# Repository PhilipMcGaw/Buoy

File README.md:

# Buoy

https://github.com/sk-t3ch/smart-buoy

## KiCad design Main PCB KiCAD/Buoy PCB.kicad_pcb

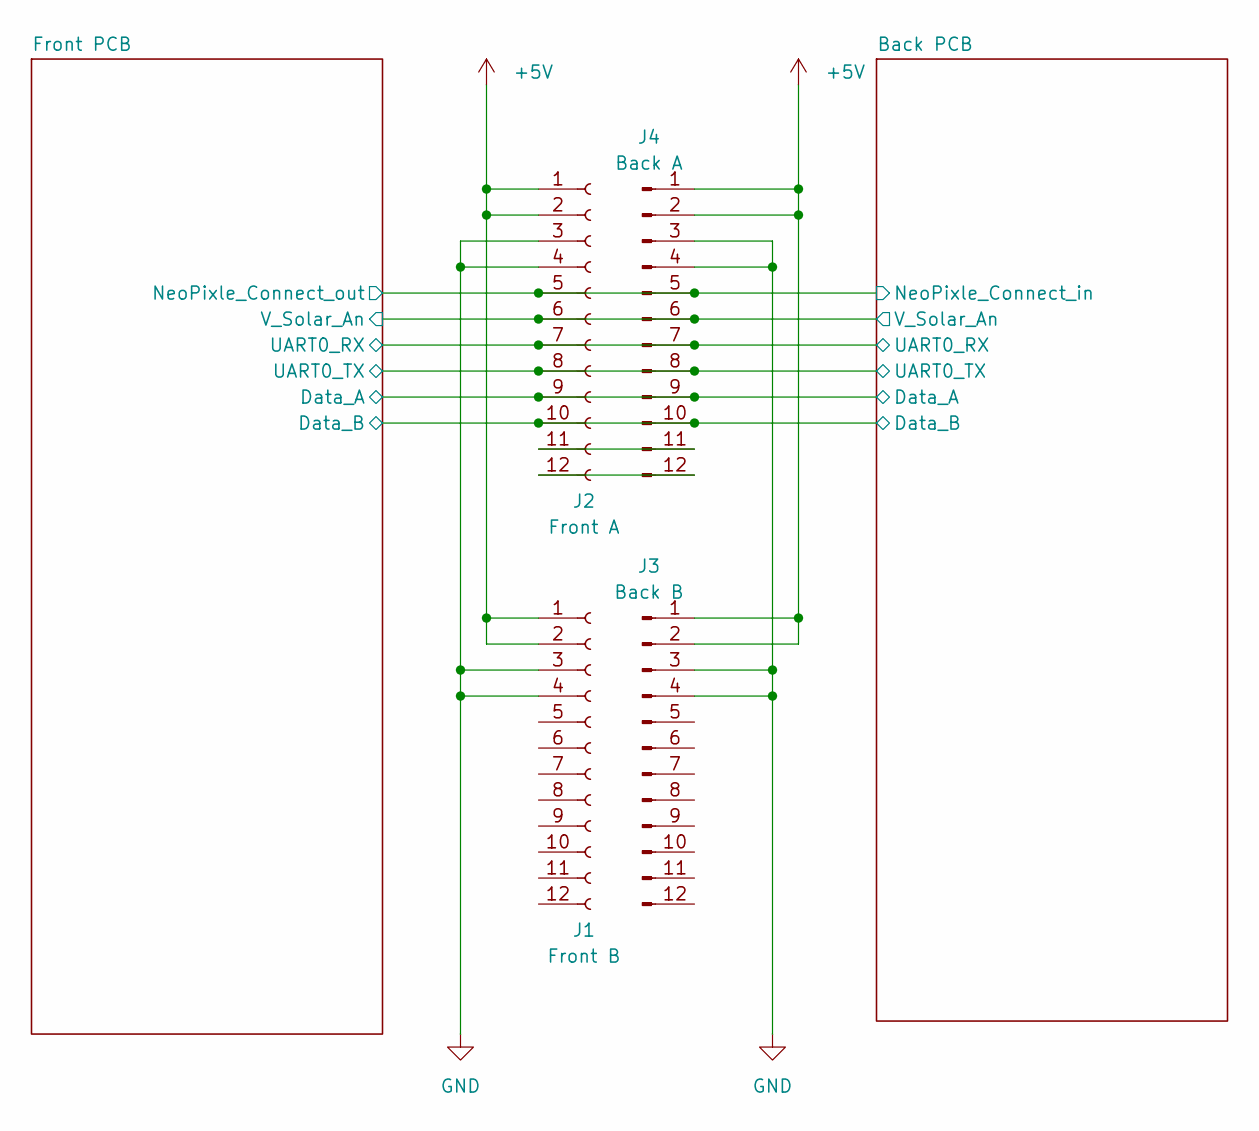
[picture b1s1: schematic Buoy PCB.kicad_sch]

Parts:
J1: Front B; PinSocket_1x12_P2.54mm_Vertical
J2: Front A; PinSocket_1x12_P2.54mm_Vertical
J3: Back B; PinHeader_1x12_P2.54mm_Vertical
J4: Back A; PinHeader_1x12_P2.54mm_Vertical

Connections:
+5V: J1.1, J1.2, J2.1, J2.2, J3.1, J3.2, J4.1, J4.2; also elsewhere on the board
/Back PCB/Data_A: J2.9, J4.9; also elsewhere on the board
/Back PCB/Data_B: J2.10, J4.10; also elsewhere on the board
/Back PCB/NeoPixle_Connect_in: J2.5, J4.5; also elsewhere on the board
/Back PCB/UART0_RX: J2.7, J4.7; also elsewhere on the board
/Back PCB/UART0_TX: J2.8, J4.8; also elsewhere on the board
/Back PCB/V_Solar_An: J2.6, J4.6; also elsewhere on the board
GND: J1.3, J1.4, J2.3, J2.4, J3.3, J3.4, J4.3, J4.4; also elsewhere on the board
unnamed: J2.11, J4.11
unnamed: J2.12, J4.12

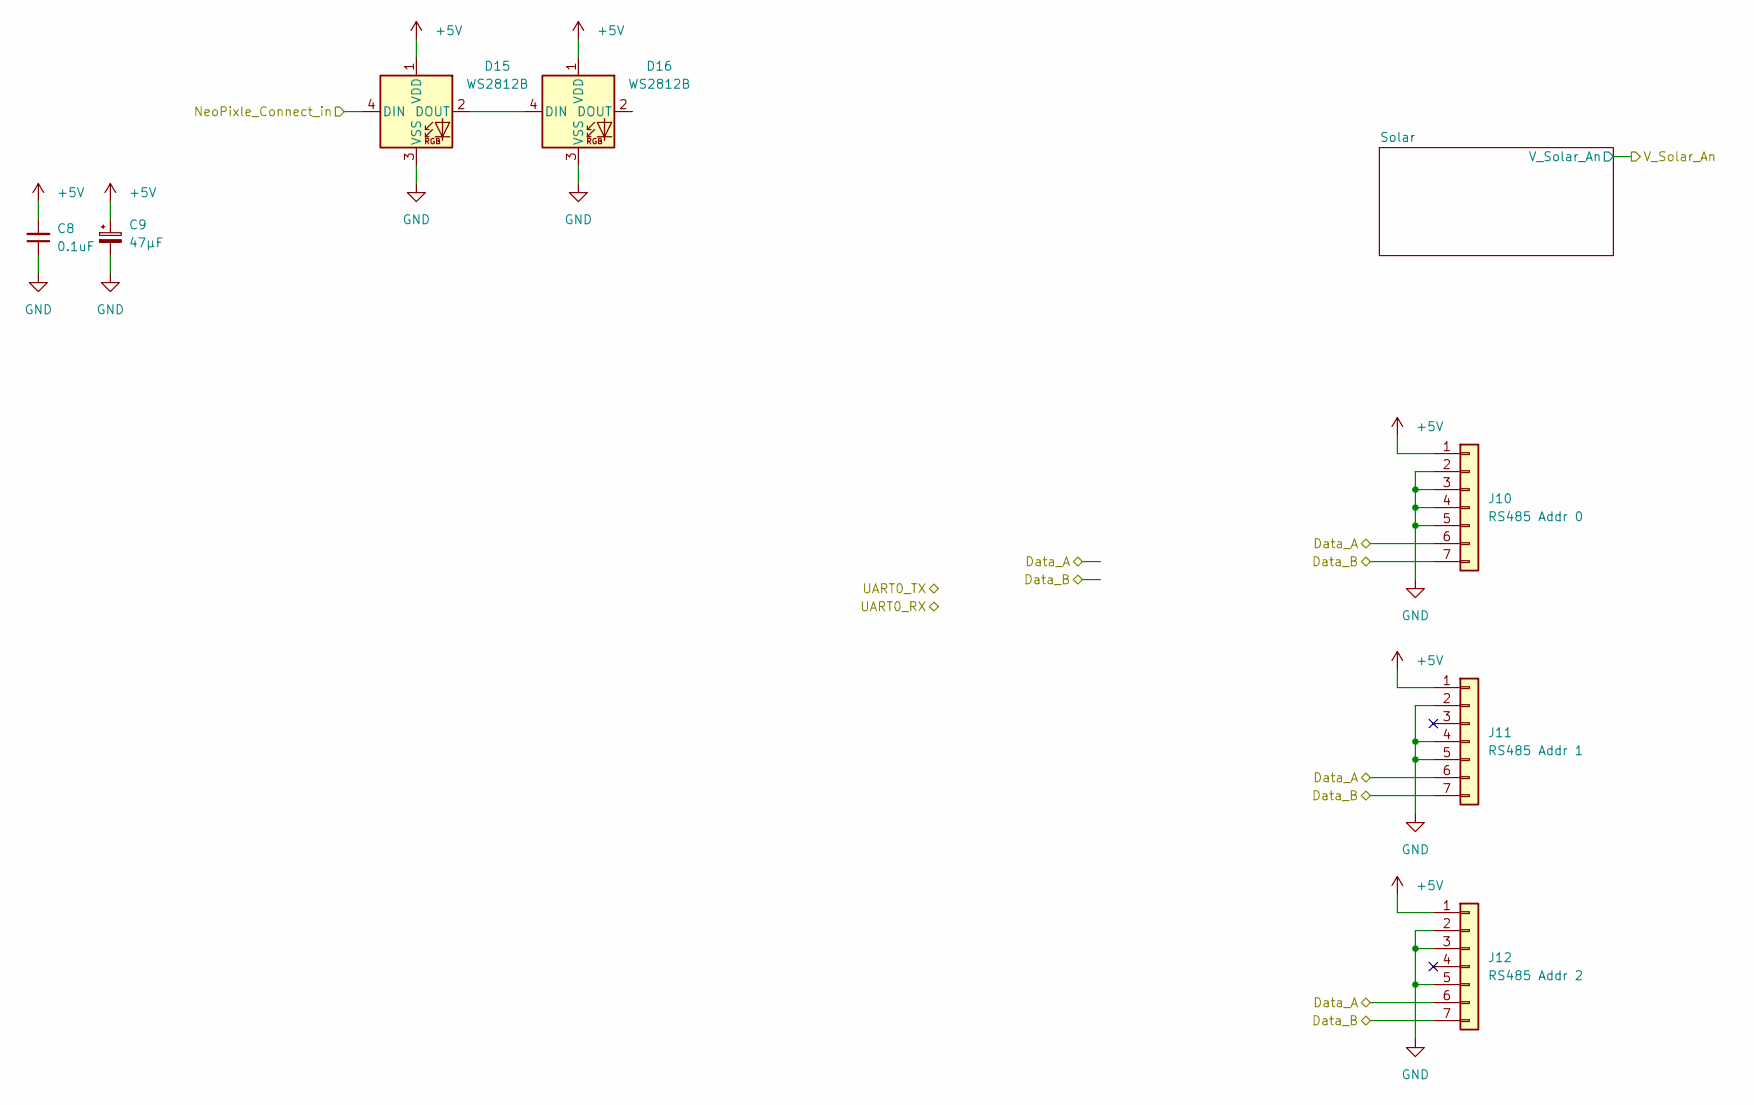
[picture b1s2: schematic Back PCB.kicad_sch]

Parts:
C8: 0.1uF; C_0805_2012Metric_Pad1.18x1.45mm_HandSolder
C9: 47μF; CP_Elec_5x5.9
D15, D16: WS2812B; LED_WS2812B_PLCC4_5.0x5.0mm_P3.2mm
J10: RS485 Addr 0; JST_EH_S7B-EH_1x07_P2.50mm_Horizontal
J11: RS485 Addr 1; JST_EH_S7B-EH_1x07_P2.50mm_Horizontal
J12: RS485 Addr 2; JST_EH_S7B-EH_1x07_P2.50mm_Horizontal

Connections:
+5V: C8.2, C9.1, D15.1 (VDD), D16.1 (VDD), J10.1, J11.1, J12.1; also elsewhere on the board
/Back PCB/Data_A: J10.6, J11.6, J12.6; also elsewhere on the board
/Back PCB/Data_B: J10.7, J11.7, J12.7; also elsewhere on the board
/Back PCB/NeoPixle_Connect_in: D15.4 (DIN); also elsewhere on the board
GND: C8.1, C9.2, D15.3 (VSS), D16.3 (VSS), J10.2, J10.3, J10.4, J10.5, J11.2, J11.4, J11.5, J12.2, J12.3, J12.5; also elsewhere on the board
unnamed: D15.2 (DOUT), D16.4 (DIN)

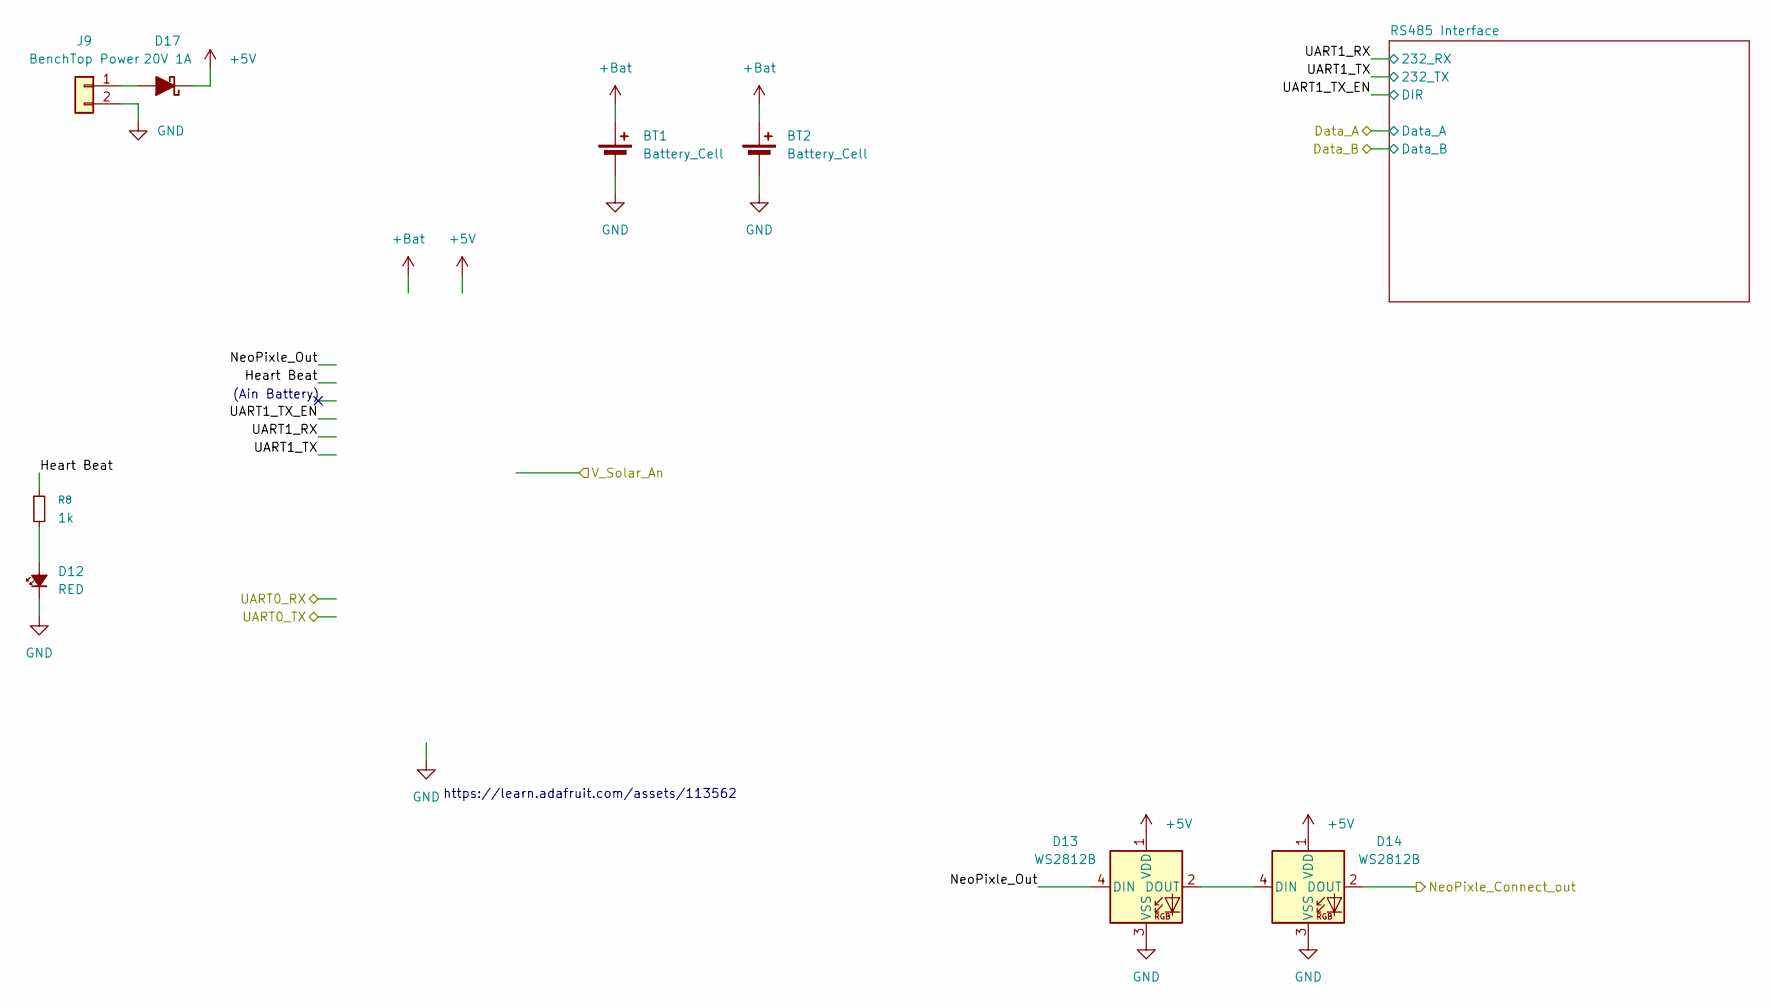
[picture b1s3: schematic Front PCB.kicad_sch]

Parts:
BT1, BT2: Battery_Cell; BatteryHolder_Keystone_1042_1x18650
D12: RED; LED_0805_2012Metric_Pad1.15x1.40mm_HandSolder
D13, D14: WS2812B; LED_WS2812B_PLCC4_5.0x5.0mm_P3.2mm
D17: 20V 1A; D_0805_2012Metric_Pad1.15x1.40mm_HandSolder; Mouser 581-SD0805S020S1R0
J9: BenchTop Power; JST_EH_S2B-EH_1x02_P2.50mm_Horizontal
R8: 1k; R_0805_2012Metric_Pad1.20x1.40mm_HandSolder

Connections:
+5V: D13.1 (VDD), D14.1 (VDD), D17.1 (K); also elsewhere on the board
+Bat: BT1.1 (+), BT2.1 (+); also elsewhere on the board
/Back PCB/NeoPixle_Connect_in: D14.2 (DOUT); also elsewhere on the board
/Front PCB/Heart Beat: R8.1; also elsewhere on the board
/Front PCB/NeoPixle_Out: D13.4 (DIN); also elsewhere on the board
GND: BT1.2 (-), BT2.2 (-), D12.1 (K), D13.3 (VSS), D14.3 (VSS), J9.2; also elsewhere on the board
unnamed: D12.2 (A), R8.2
unnamed: D13.2 (DOUT), D14.4 (DIN)
unnamed: D17.2 (A), J9.1

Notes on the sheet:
(Ain Battery)
https://learn.adafruit.com/assets/113562

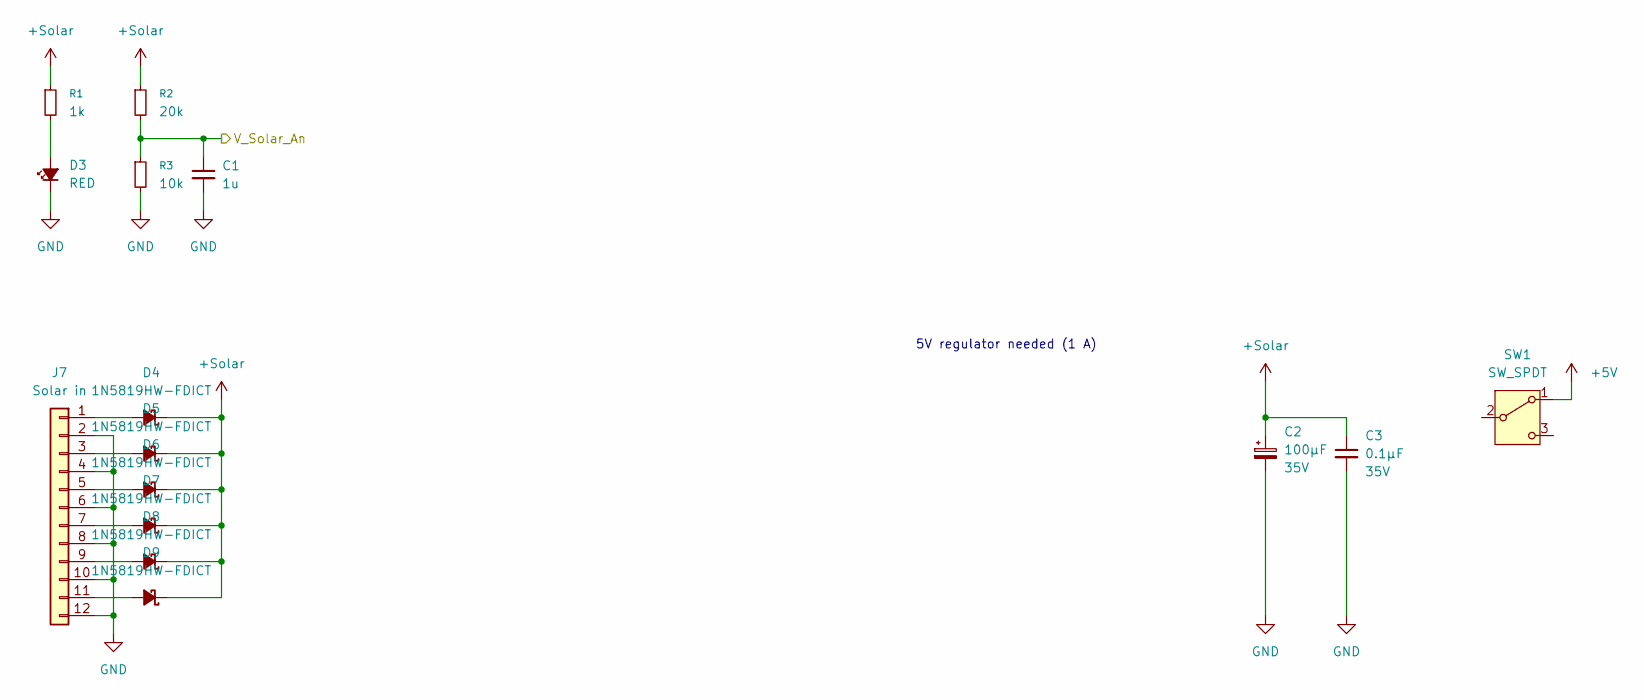
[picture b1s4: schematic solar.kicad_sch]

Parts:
C1: 1u; C_0805_2012Metric_Pad1.18x1.45mm_HandSolder
C2: 100μF; CP_Elec_5x5.9; Voltage 35V; Farnell 2690258
C3: 0.1μF; C_0805_2012Metric_Pad1.18x1.45mm_HandSolder; Voltage 35V; Farnell 2773206
D3: RED; LED_0805_2012Metric_Pad1.15x1.40mm_HandSolder
D4, D5, D6, D7, D8, D9: 1N5819HW-FDICT; D_SOD-123
J7: Solar in; JST_EH_S12B-EH_1x12_P2.50mm_Horizontal
R1: 1k; R_0805_2012Metric_Pad1.20x1.40mm_HandSolder
R2: 20k; R_0805_2012Metric_Pad1.20x1.40mm_HandSolder
R3: 10k; R_0805_2012Metric_Pad1.20x1.40mm_HandSolder
SW1: SW_SPDT; SW_Slide_SPDT_Angled_CK_OS102011MA1Q

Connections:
+5V: SW1.1 (A_1); also elsewhere on the board
+Solar: C2.1, C3.1, D4.1 (K), D5.1 (K), D6.1 (K), D7.1 (K), D8.1 (K), D9.1 (K), R1.1, R2.1
/Back PCB/V_Solar_An: C1.1, R2.2, R3.1; also elsewhere on the board
GND: C1.2, C2.2, C3.2, D3.1 (K), J7.2, J7.4, J7.6, J7.8, J7.10, J7.12, R3.2; also elsewhere on the board
unnamed: D3.2 (A), R1.2
unnamed: D4.2 (A), J7.1
unnamed: D5.2 (A), J7.3
unnamed: D6.2 (A), J7.5
unnamed: D7.2 (A), J7.7
unnamed: D8.2 (A), J7.9
unnamed: D9.2 (A), J7.11

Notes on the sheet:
5V regulator needed (1 A)

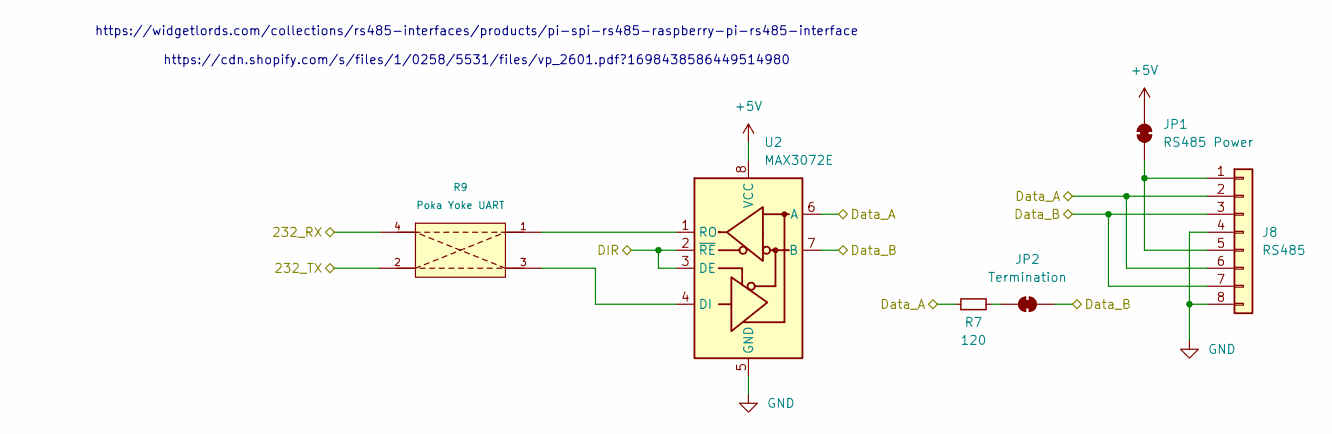
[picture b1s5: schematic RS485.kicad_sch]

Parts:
J8: RS485; JST_EH_S8B-EH_1x08_P2.50mm_Horizontal
JP1: RS485 Power; SolderJumper-2_P1.3mm_Bridged_RoundedPad1.0x1.5mm
JP2: Termination; SolderJumper-2_P1.3mm_Bridged_RoundedPad1.0x1.5mm
R7: 120; R_0805_2012Metric_Pad1.20x1.40mm_HandSolder
R9: Poka Yoke UART; Poka yoke UART Solder
U2: MAX3072E; SOIC-8_3.9x4.9mm_P1.27mm

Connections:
+5V: JP1.2 (B), U2.8 (VCC); also elsewhere on the board
/Back PCB/Data_A: J8.2, J8.6, R7.1, U2.6 (A); also elsewhere on the board
/Back PCB/Data_B: J8.3, J8.7, JP2.1 (A), U2.7 (B); also elsewhere on the board
/Front PCB/UART1_RX: R9.4; also elsewhere on the board
/Front PCB/UART1_TX: R9.2; also elsewhere on the board
/Front PCB/UART1_TX_EN: U2.2 (~RE), U2.3 (DE); also elsewhere on the board
GND: J8.4, J8.8, U2.5 (GND); also elsewhere on the board
unnamed: J8.1, J8.5, JP1.1 (A)
unnamed: JP2.2 (B), R7.2
unnamed: R9.3, U2.4 (DI)
unnamed: R9.1, U2.1 (RO)

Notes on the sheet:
https://widgetlords.com/collections/rs485-interfaces/products/pi-spi-rs485-raspberry-pi-rs485-interface https://cdn.shopify.com/s/files/1/0258/5531/files/vp_2601.pdf?1698438586449514980

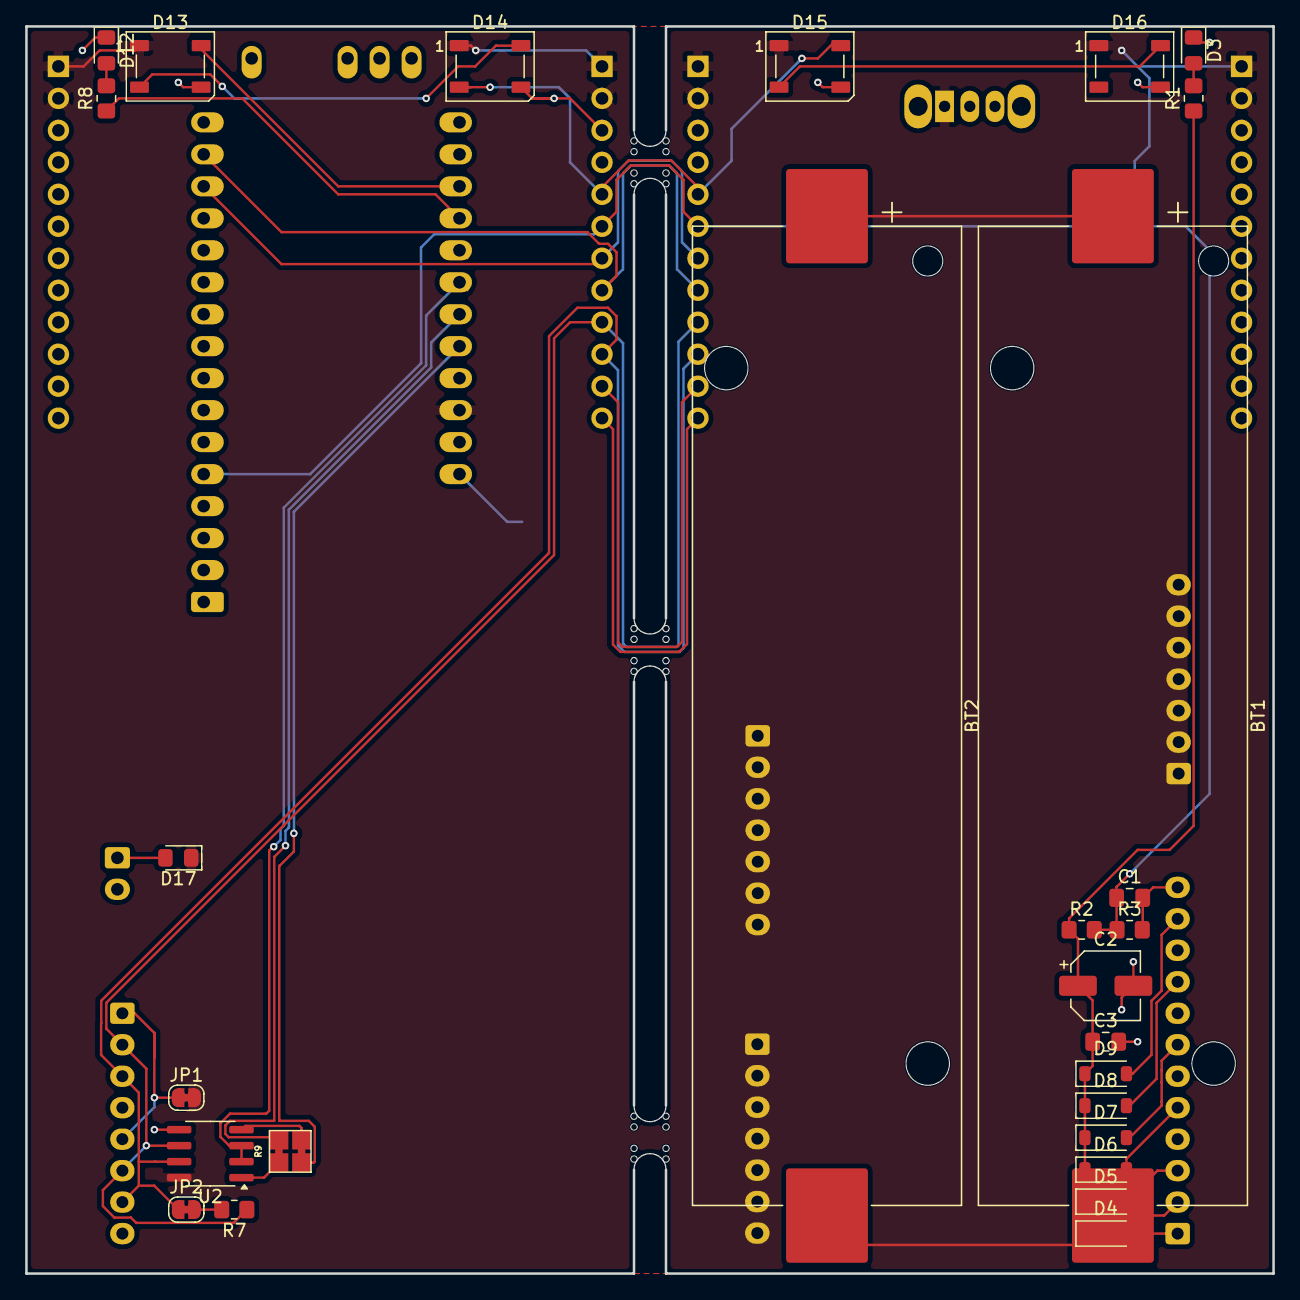
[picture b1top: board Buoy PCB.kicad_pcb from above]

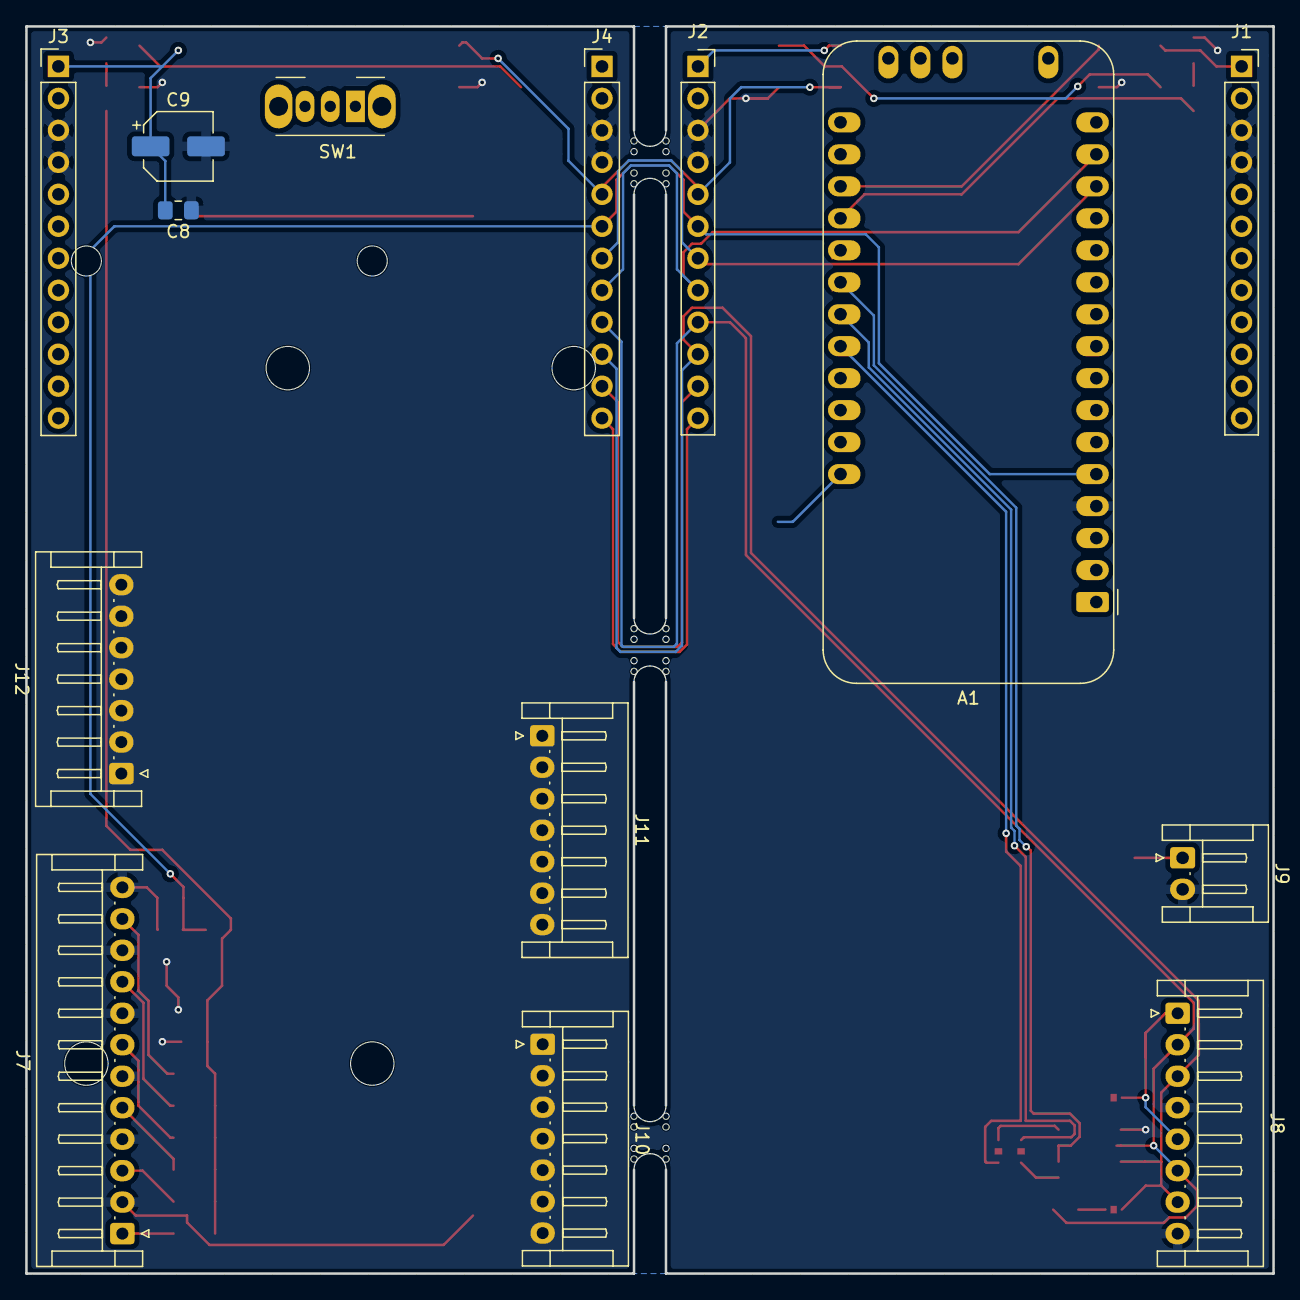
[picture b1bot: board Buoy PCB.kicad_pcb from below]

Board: 2 copper layers, 99.1 x 99.1 mm, 44 parts (14 on the bottom side), 32 nets.

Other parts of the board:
A1: Adafruit_Feather_M0_RFM9x_LoRa_Radio; Adafruit_Feather_M0_RFM
mouse-bite-2.54mm-slot, mouse-bite-2.54mm-slot#2, mouse-bite-2.54mm-slot#3: VAL**; MouseBite Slot 2.54 x 2.54mm

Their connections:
+5V: A1.26 (USB); also elsewhere on the board
+Bat: A1.28 (VBAT); also elsewhere on the board
/Back PCB/UART0_RX: A1.14 (RX/D0); also elsewhere on the board
/Back PCB/UART0_TX: A1.15 (TX/D1); also elsewhere on the board
/Back PCB/V_Solar_An: A1.5 (DAC0/A0); also elsewhere on the board
/Front PCB/Heart Beat: A1.20 (D6); also elsewhere on the board
/Front PCB/NeoPixle_Out: A1.19 (D5); also elsewhere on the board
/Front PCB/UART1_RX: A1.23 (D11); also elsewhere on the board
/Front PCB/UART1_TX: A1.24 (D12); also elsewhere on the board
/Front PCB/UART1_TX_EN: A1.22 (D10); also elsewhere on the board
GND: A1.4 (GND); also elsewhere on the board

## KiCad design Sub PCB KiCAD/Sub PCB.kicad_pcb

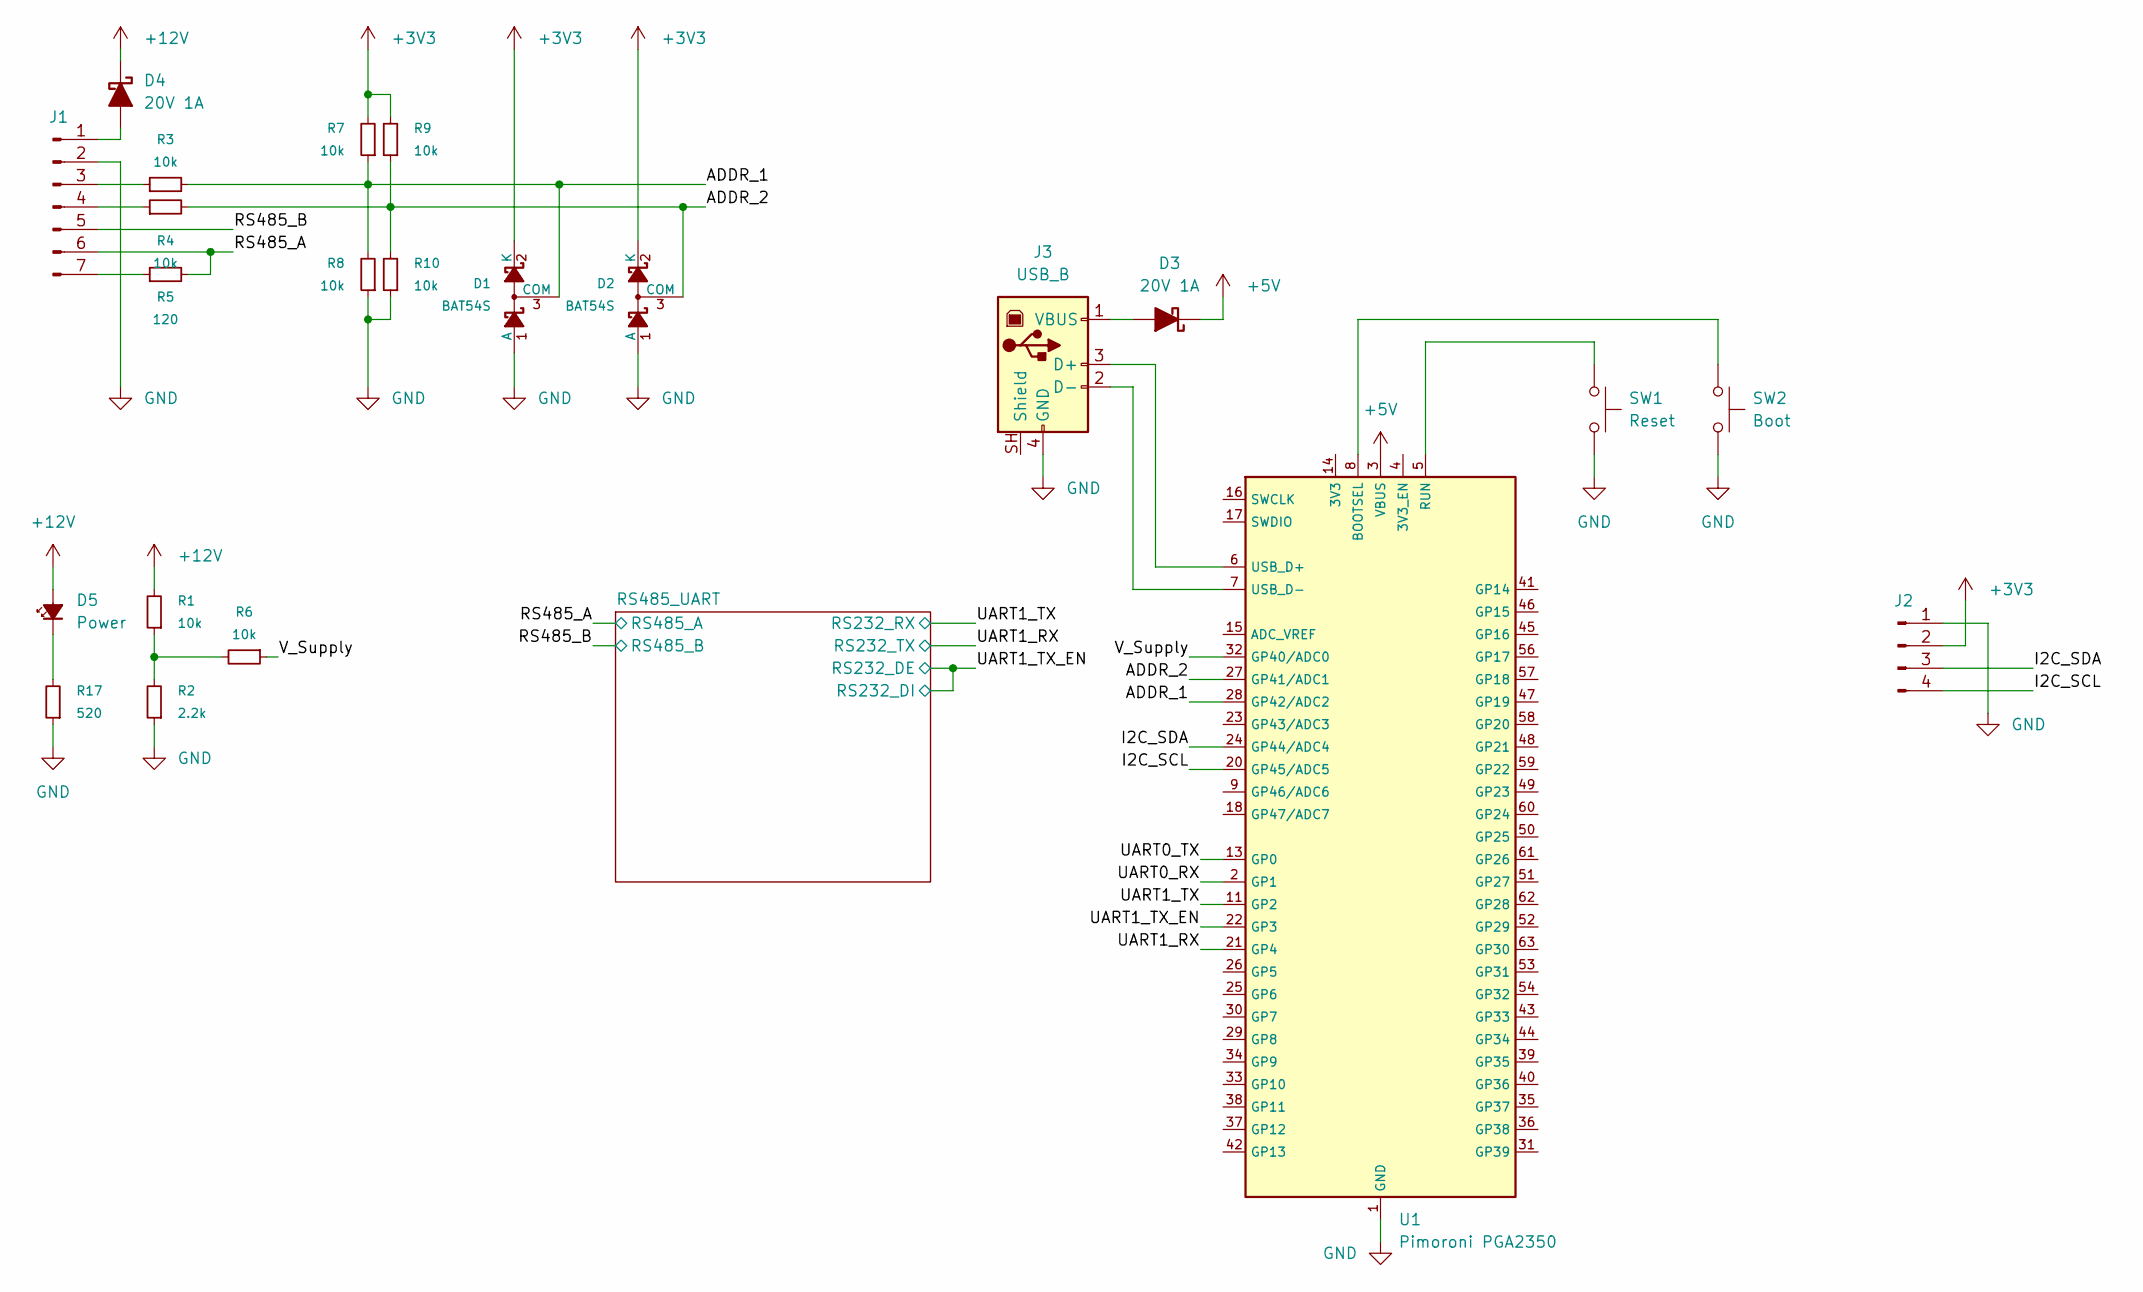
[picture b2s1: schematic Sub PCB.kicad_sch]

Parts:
D1, D2: BAT54S; SOT-23
D3, D4: 20V 1A; D_0805_2012Metric_Pad1.15x1.40mm_HandSolder; Mouser 581-SD0805S020S1R0
D5: Power; LED_0805_2012Metric_Pad1.15x1.40mm_HandSolder
J1: PinHeader_1x07_P2.54mm_Vertical
J2: PinHeader_1x04_P2.54mm_Vertical
J3: USB_B
R1, R3, R4, R6, R7, R8, R9, R10: 10k; R_0805_2012Metric_Pad1.20x1.40mm_HandSolder
R2: 2.2k; R_0805_2012Metric_Pad1.20x1.40mm_HandSolder
R5: 120; R_0805_2012Metric_Pad1.20x1.40mm_HandSolder
R17: 520; R_0805_2012Metric_Pad1.20x1.40mm_HandSolder
SW1: Reset; SW_PUSH-12mm
SW2: Boot; SW_PUSH-12mm
U1: Pimoroni PGA2350; PGA2350

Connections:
+3V3: D1.2 (K), D2.2 (K), J2.2, R7.2, R9.2; also elsewhere on the board
+5V: D3.1 (K), U1.3 (VBUS)
+12V: D4.1 (K), D5.2 (A), R1.2
/ADDR_1: D1.3 (COM), R3.2, R7.1, R8.2, U1.28 (GP42/ADC2)
/ADDR_2: D2.3 (COM), R4.2, R9.1, R10.2, U1.27 (GP41/ADC1)
/I2C_SCL: J2.4, U1.20 (GP45/ADC5)
/I2C_SDA: J2.3, U1.24 (GP44/ADC4)
/RS485_A: J1.6, R5.2; also elsewhere on the board
/RS485_B: J1.5; also elsewhere on the board
/UART0_RX: U1.2 (GP1)
/UART0_TX: U1.13 (GP0)
/UART1_RX: U1.21 (GP4); also elsewhere on the board
/UART1_TX: U1.11 (GP2); also elsewhere on the board
/UART1_TX_EN: U1.22 (GP3); also elsewhere on the board
/V_Supply: R6.1, U1.32 (GP40/ADC0)
GND: D1.1 (A), D2.1 (A), J1.2, J2.1, J3.4 (GND), R2.1, R8.1, R10.1, R17.1, SW1.2, SW2.2, U1.1 (GND), U1.10 (GND), U1.12 (GND), U1.19 (GND), U1.55 (GND), U1.64 (GND); also elsewhere on the board
unnamed: D3.2 (A), J3.1 (VBUS)
unnamed: D4.2 (A), J1.1
unnamed: D5.1 (K), R17.2
unnamed: J1.3, R3.1
unnamed: J1.4, R4.1
unnamed: J1.7, R5.1
unnamed: J3.3 (D+), U1.6 (USB_D+)
unnamed: J3.2 (D-), U1.7 (USB_D-)
unnamed: R1.1, R2.2, R6.2
unnamed: SW2.1, U1.8 (BOOTSEL)
unnamed: SW1.1, U1.5 (RUN)

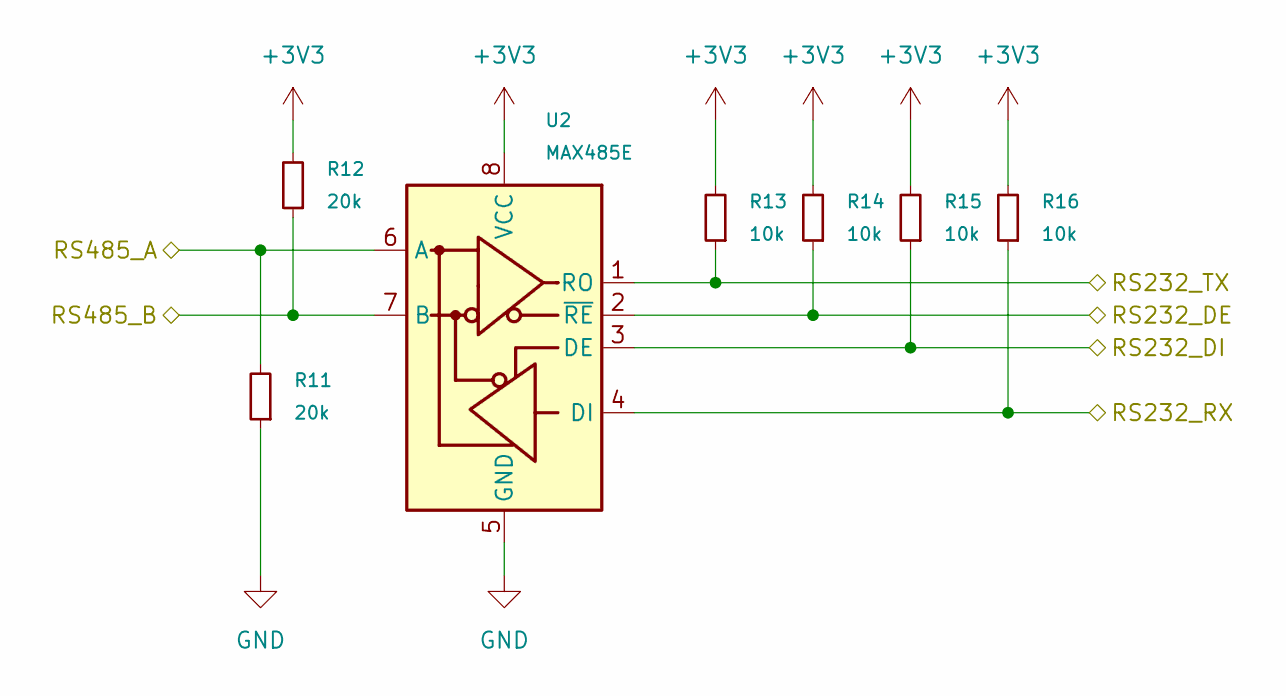
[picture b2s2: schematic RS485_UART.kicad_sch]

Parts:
R11, R12: 20k; R_0805_2012Metric_Pad1.20x1.40mm_HandSolder
R13, R14, R15, R16: 10k; R_0805_2012Metric_Pad1.20x1.40mm_HandSolder
U2: MAX485E; SOIC-8_3.9x4.9mm_P1.27mm

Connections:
+3V3: R12.2, R13.2, R14.2, R15.2, R16.2, U2.8 (VCC); also elsewhere on the board
/RS485_A: R11.2, U2.6 (A); also elsewhere on the board
/RS485_B: R12.1, U2.7 (B); also elsewhere on the board
/UART1_RX: R13.1, U2.1 (RO); also elsewhere on the board
/UART1_TX: R16.1, U2.4 (DI); also elsewhere on the board
/UART1_TX_EN: R14.1, R15.1, U2.2 (~RE), U2.3 (DE); also elsewhere on the board
GND: R11.1, U2.5 (GND); also elsewhere on the board

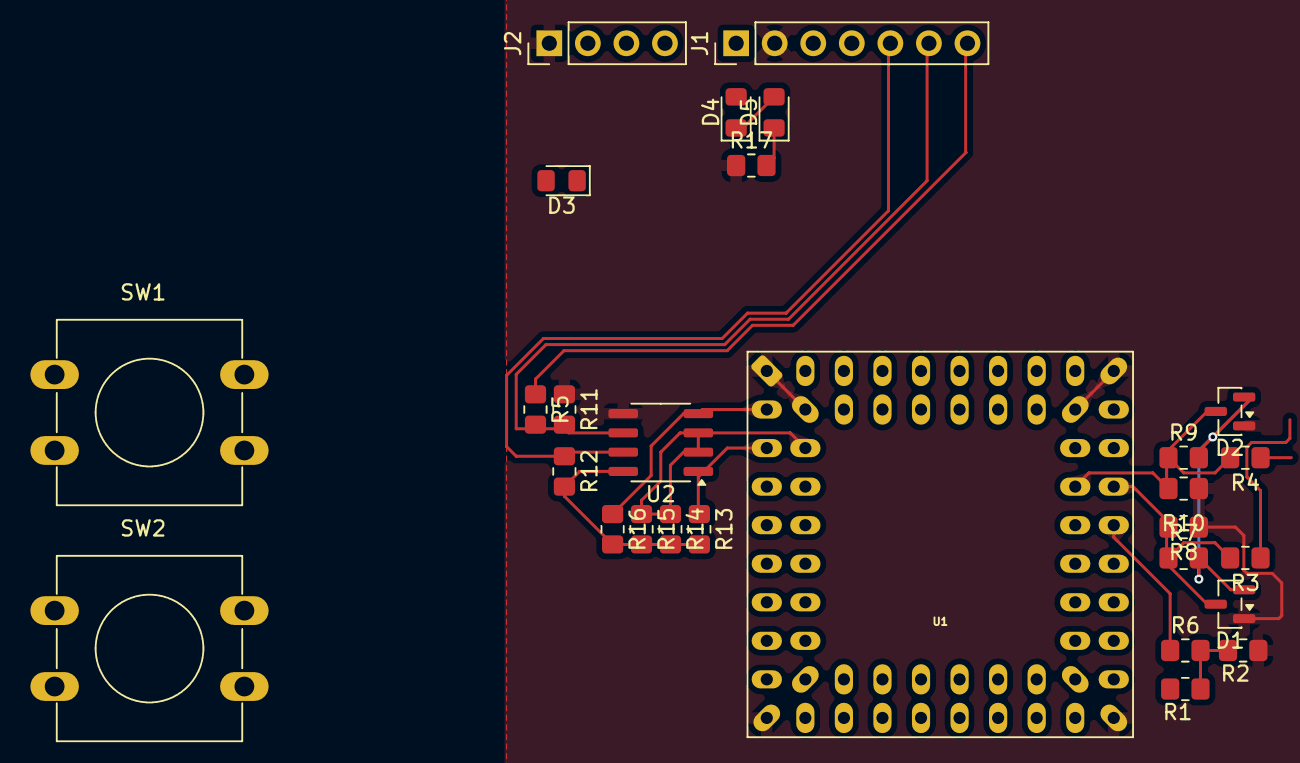
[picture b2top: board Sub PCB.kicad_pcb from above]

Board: 2 copper layers, 28 parts (0 on the bottom side), 22 nets.

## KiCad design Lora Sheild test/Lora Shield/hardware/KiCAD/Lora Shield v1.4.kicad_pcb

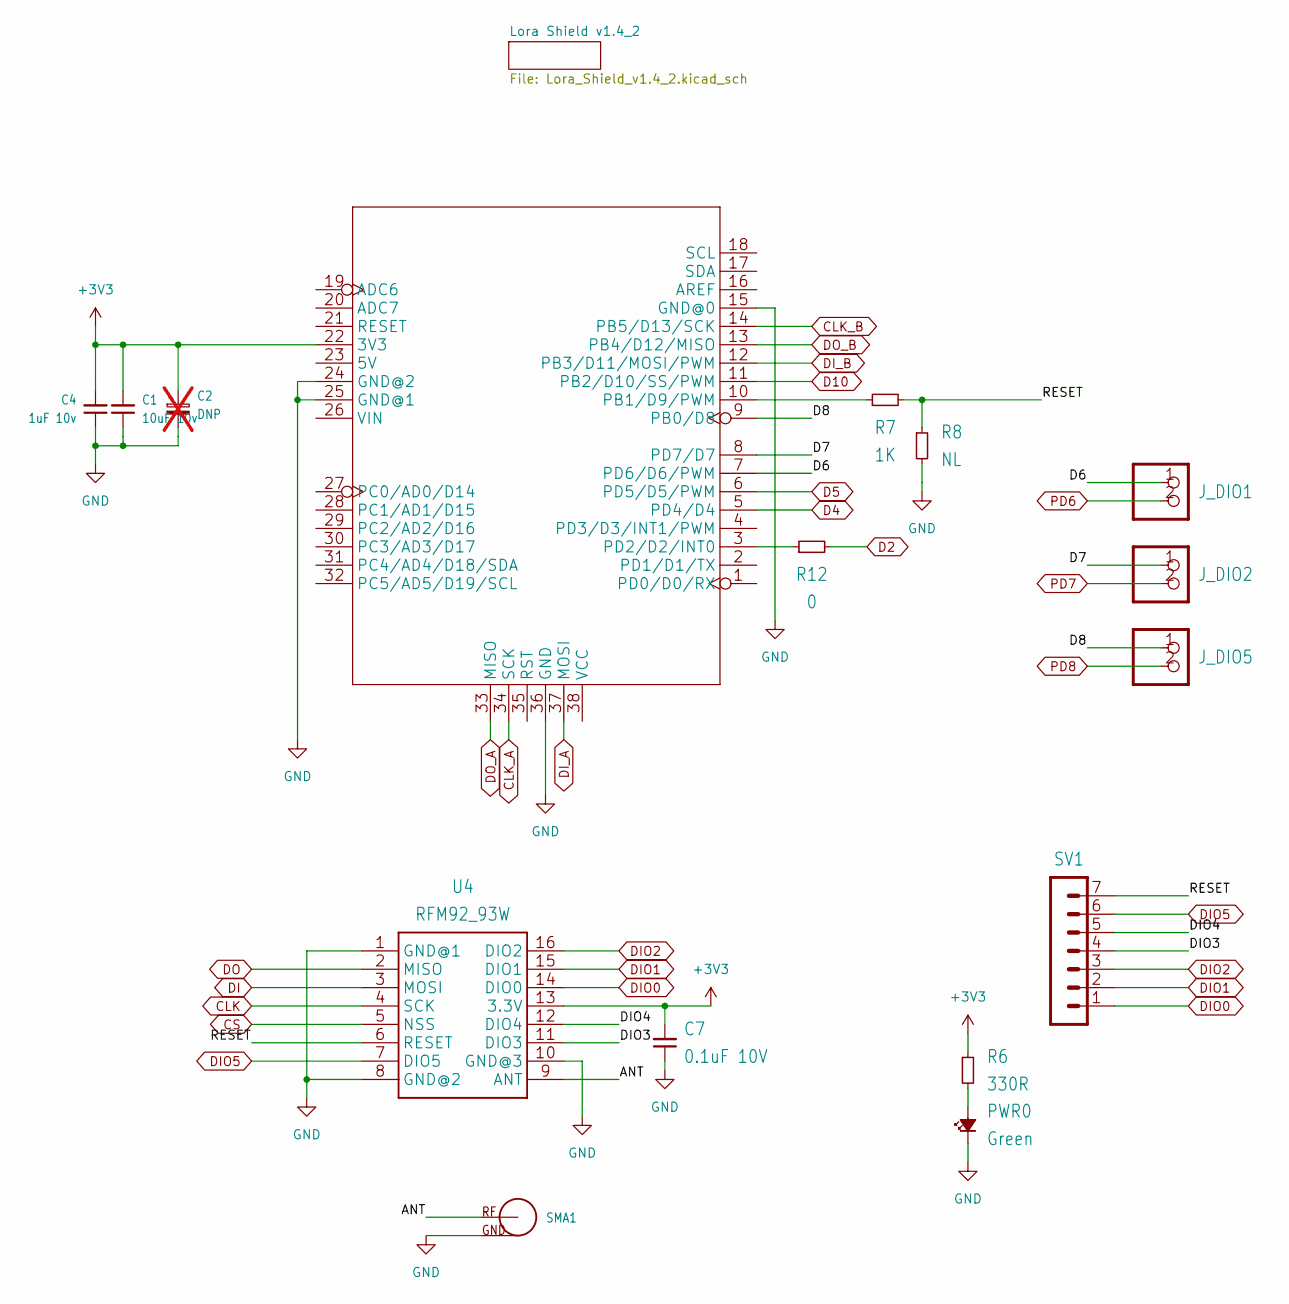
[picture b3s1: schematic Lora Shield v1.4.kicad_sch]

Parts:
C1: 10uF 10v; C0805
C2: DNP; AVX-A; not fitted
C4: 1uF 10v; C0805
C7: 0.1uF 10V; C0402
J_DIO1, J_DIO2, J_DIO5: PINHD-1X2; 1X02
PWR0: Green; CHIP-LED0603
R6: 330R; R0402
R7: 1K; R0402
R8: NL; R0402
R12: 0; R0402
SMA1: SMA-KWE
SV1: MA07-1
U4: RFM92_93W
U5: MOUDLE_ARDUINO-38P328P_NO_VIA; MOUDLE_ARDUINO-328P--

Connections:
3V3: C1.2, C2.1, C2.+, C4.2, C7.2, R6.1, U4.13 (3.3V), U5.22 (3V3); also elsewhere on the board
ANT: SMA1.1 (SIG), U4.9 (ANT)
CLK: U4.4 (SCK); also elsewhere on the board
CLK_A: U5.34 (SCK); also elsewhere on the board
CLK_B: U5.14 (PB5/D13/SCK); also elsewhere on the board
CS: U4.5 (NSS); also elsewhere on the board
D4: U5.5 (PD4/D4); also elsewhere on the board
D5: U5.6 (PD5/D5/PWM); also elsewhere on the board
D6: J_DIO1.1, U5.7 (PD6/D6/PWM)
D7: J_DIO2.1, U5.8 (PD7/D7)
D8: J_DIO5.1, U5.9 (PB0/D8)
D10: U5.11 (PB2/D10/SS/PWM); also elsewhere on the board
DI: U4.3 (MOSI); also elsewhere on the board
DIO0: SV1.1, U4.14 (DIO0); also elsewhere on the board
DIO1: SV1.2, U4.15 (DIO1); also elsewhere on the board
DIO2: SV1.3, U4.16 (DIO2); also elsewhere on the board
DIO3: SV1.4, U4.11 (DIO3)
DIO4: SV1.5, U4.12 (DIO4)
DIO5: SV1.6, U4.7 (DIO5); also elsewhere on the board
DI_A: U5.37 (MOSI); also elsewhere on the board
DI_B: U5.12 (PB3/D11/MOSI/PWM); also elsewhere on the board
DO: U4.2 (MISO); also elsewhere on the board
DO_A: U5.33 (MISO); also elsewhere on the board
DO_B: U5.13 (PB4/D12/MISO); also elsewhere on the board
GND: C1.1, C2.2, C2.-, C4.1, C7.1, PWR0.1 (K), PWR0.C, R8.2, SMA1.2 (GND), SMA1.3 (GND), SMA1.4 (GND), SMA1.5 (GND), U4.1 (GND@1), U4.8 (GND@2), U4.10 (GND@3), U5.15 (GND@0), U5.24 (GND@2), U5.25 (GND@1), U5.36 (GND); also elsewhere on the board
unnamed 30: R12.1, U5.3 (PD2/D2/INT0); also elsewhere on the board
unnamed: PWR0.2 (A), PWR0.A, R6.2
unnamed: R7.1, U5.10 (PB1/D9/PWM)
PD6: J_DIO1.2; also elsewhere on the board
PD7: J_DIO2.2; also elsewhere on the board
PD8: J_DIO5.2; also elsewhere on the board
RESET: R7.2, R8.1, SV1.7, U4.6 (RESET)
